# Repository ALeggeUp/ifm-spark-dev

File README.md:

# IFM Spark Dev Board

What is it?
-----------

IFM Spark Dev Board is a minimal Cortex-M0 dev board for experimentation.
The firmware is an example project that uses Gradle to build and test an embedded application.
It uses the examples included with the CppUTest project to show how it would work, the
embedded application doesn't do anything other than contain the objects to test.

Contributors
------------

* [Stephen Legge](https://github.com/slegge)

System requirements
-------------------

Gradle requires Java, but with the included gradlew that should be all that is needed
to build the firmware image.  This project as part of its initialization should pull
down the toolchain needed to build the firmware image.

For each operating system the requirements are similar, generally a Gcc or Clang
toolchain needs to be available for Gradle to use to build the tests.

In Windows, a standard install of Cygwin with gcc toolchain has been tested.

In Mac OS X, a default install of Xcode provides the Clang toolchain.

In Linux, standard gcc/g++ devel packages usually work fine.

Building
--------

If you have Gradle 3.0+ installed, you can just use

`gradle clean build`

or to use the bundled gradlew (Gradle Wrapper) use:

`./gradlew clean build`

Executing
---------

The Gradle build will create the firmware image and the CppUTest unit test runner.
The firmware image is meant to be loaded on the hardware, you'll need to load it
onto the hardware manually.  With an mbed board like a Nucleo board, it is just a
matter of copying the image to the mass storage device.

The CppUTest unit test runner is called utestrunner located under build/utestrunner/...

# License

This work is licensed under the Creative Commons Attribution 4.0 International License. To view a copy of this license, visit http://creativecommons.org/licenses/by/4.0/ or send a
letter to Creative Commons, PO Box 1866, Mountain View, CA 94042, USA.

Disclaimer
----------

THIS SOFTWARE IS PROVIDED BY THE COPYRIGHT HOLDERS AND CONTRIBUTORS "AS IS"
AND ANY EXPRESS OR IMPLIED WARRANTIES, INCLUDING, BUT NOT LIMITED TO, THE
IMPLIED WARRANTIES OF MERCHANTABILITY AND FITNESS FOR A PARTICULAR PURPOSE
ARE DISCLAIMED. IN NO EVENT SHALL THE COPYRIGHT OWNER OR CONTRIBUTORS BE
LIABLE FOR ANY DIRECT, INDIRECT, INCIDENTAL, SPECIAL, EXEMPLARY, OR
CONSEQUENTIAL DAMAGES (INCLUDING, BUT NOT LIMITED TO, PROCUREMENT OF
SUBSTITUTE GOODS OR SERVICES; LOSS OF USE, DATA, OR PROFITS; OR BUSINESS
INTERRUPTION) HOWEVER CAUSED AND ON ANY THEORY OF LIABILITY, WHETHER IN
CONTRACT, STRICT LIABILITY, OR TORT (INCLUDING NEGLIGENCE OR OTHERWISE)
ARISING IN ANY WAY OUT OF THE USE OF THIS SOFTWARE, EVEN IF ADVISED OF THE
POSSIBILITY OF SUCH DAMAGE.

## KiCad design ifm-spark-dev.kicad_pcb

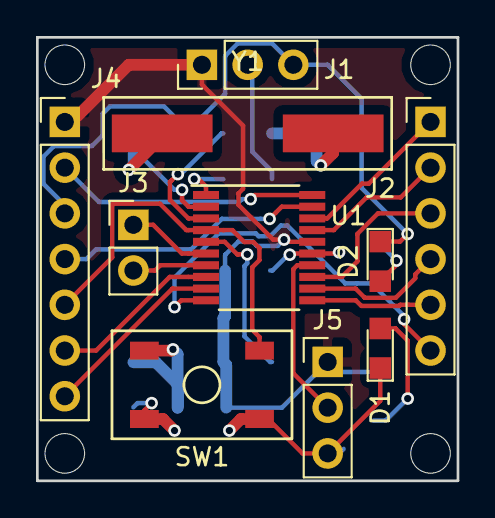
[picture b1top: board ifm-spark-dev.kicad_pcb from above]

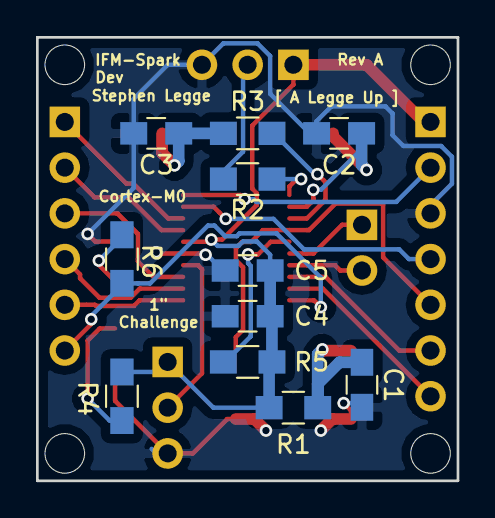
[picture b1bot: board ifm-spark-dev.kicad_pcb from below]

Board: 2 copper layers, 23.4 x 24.6 mm, 21 parts (11 on the bottom side), 25 nets.

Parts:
C1: 100nF; C_0805_HandSoldering
C2, C3: 20pF; C_0805_HandSoldering
C4: 1uF; C_0805_HandSoldering
C5: 10nF; C_0805_HandSoldering
D1, D2: LED; LED_0805
J1, J5: CONN_01X03_MALE; Pin_Header_Straight_1x03_Pitch2.54mm
J2: CONN_01X06; Pin_Header_Straight_1x06_Pitch2.54mm
J3: CONN_01X02; Pin_Header_Straight_1x02_Pitch2.54mm
J4: CONN_01X07; Pin_Header_Straight_1x07_Pitch2.54mm
R1, R4, R6: 1K; R_0805_HandSoldering
R2: 10K; R_0805_HandSoldering
R3: 390; R_0805_HandSoldering
R5: 0; R_0805_HandSoldering
SW1: PTS525-SM15; PTS525_SM15_SMTR2_LFS
U1: STM32F030x4; TSSOP-20_4.4x6.5mm_Pitch0.65mm
Y1: 8MHz; ABLS-8.000MHZ-B4-T

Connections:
+3V3: C4.1, C5.1, J1.1, J4.1, J5.1, R1.1, R4.2, R5.1, U1.16
/BOOT0: R2.1, U1.1
/IR_SIGNAL: J5.2, U1.14
/NRST: J4.5, SW1.2, U1.4
/PA4: J2.6, R6.1, U1.10
/PA5: J2.5, U1.11
/PA6: J2.4, U1.12
/PA7: J2.3, U1.13
/PA9: J2.2, U1.17
/PA10: J2.1, U1.18
/RX: J4.7, U1.9
/SWCLK: J4.2, U1.20
/SWDIO: J4.4, U1.19
/TX: J4.6, U1.8
GND: C1.2, C2.2, C3.2, C4.2, C5.2, D1.1, D2.1, J1.3, J4.3, J5.3, SW1.3, SW1.4, U1.15
unnamed: C1.1, R1.2, SW1.1
unnamed: C2.1, U1.2, Y1.2
unnamed: C3.1, R3.2, Y1.1
unnamed: D1.2, R4.1
unnamed: D2.2, R6.2
unnamed: J1.2, R2.2
unnamed: J3.1, U1.6
unnamed: J3.2, U1.7
unnamed: R3.1, U1.3
unnamed: R5.2, U1.5

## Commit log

2017-05-24 New "IFM Spark Dev" project created
2017-05-24 Intending to use STM32F0 chip on this project, created symbol and added
2017-05-26 Add License information
2017-05-27 Pin labels for stm32 IC
2017-05-27 STM32 connected to crystal and pins to connect to external IR module
2017-06-24 Added switches symbols
2017-06-24 Digital symbols
2017-06-24 More connections, added a power LED indicator
2017-06-24 Untangle some wires
2017-06-24 Schematic cleanup
2017-06-24 Add net names to the ST-Link pins and connect the other two pins
2017-06-24 Add data fields for tactile switch
2017-06-24 Added an LED to PA4 and a pull-up to the switch
2017-06-24 Annotated schematic
2017-06-24 Associated all the easy passives and pin headers
2017-06-25 Created footprint for PTS525 SM15 SMTR2 LFS
2017-06-25 Added footprint into new resonators module for 8Mhz crystal
2017-06-25 Add meta details for crystal
2017-06-25 Change nickname of library due to conflict with built-in
2017-06-25 Associate crystal
2017-06-25 Fix unconnected crystal
2017-06-25 Initial rough layout of sub components to get a feel for layout
2017-06-25 Re-order extra GPIO pins for easier layout
2017-06-25 Rough hookup of extra GPIOs
2017-06-25 Update design rules to meet OSH Park minimums
2017-06-26 First pass at connecting all nets on the board
2017-06-26 Move some references around so they are easier to read
2017-06-26 Added some labels and identifiers and cleaned up some tracks
2017-06-26 Added images captured from KiCad 3D viewer
2017-06-27 Move firmware into firmware sub
2017-06-27 Add some detail to avoid confusion with merged in README
2017-06-27 Missed settings.gradle in firmware move
2017-06-27 Move hardware files into sub for visibility
